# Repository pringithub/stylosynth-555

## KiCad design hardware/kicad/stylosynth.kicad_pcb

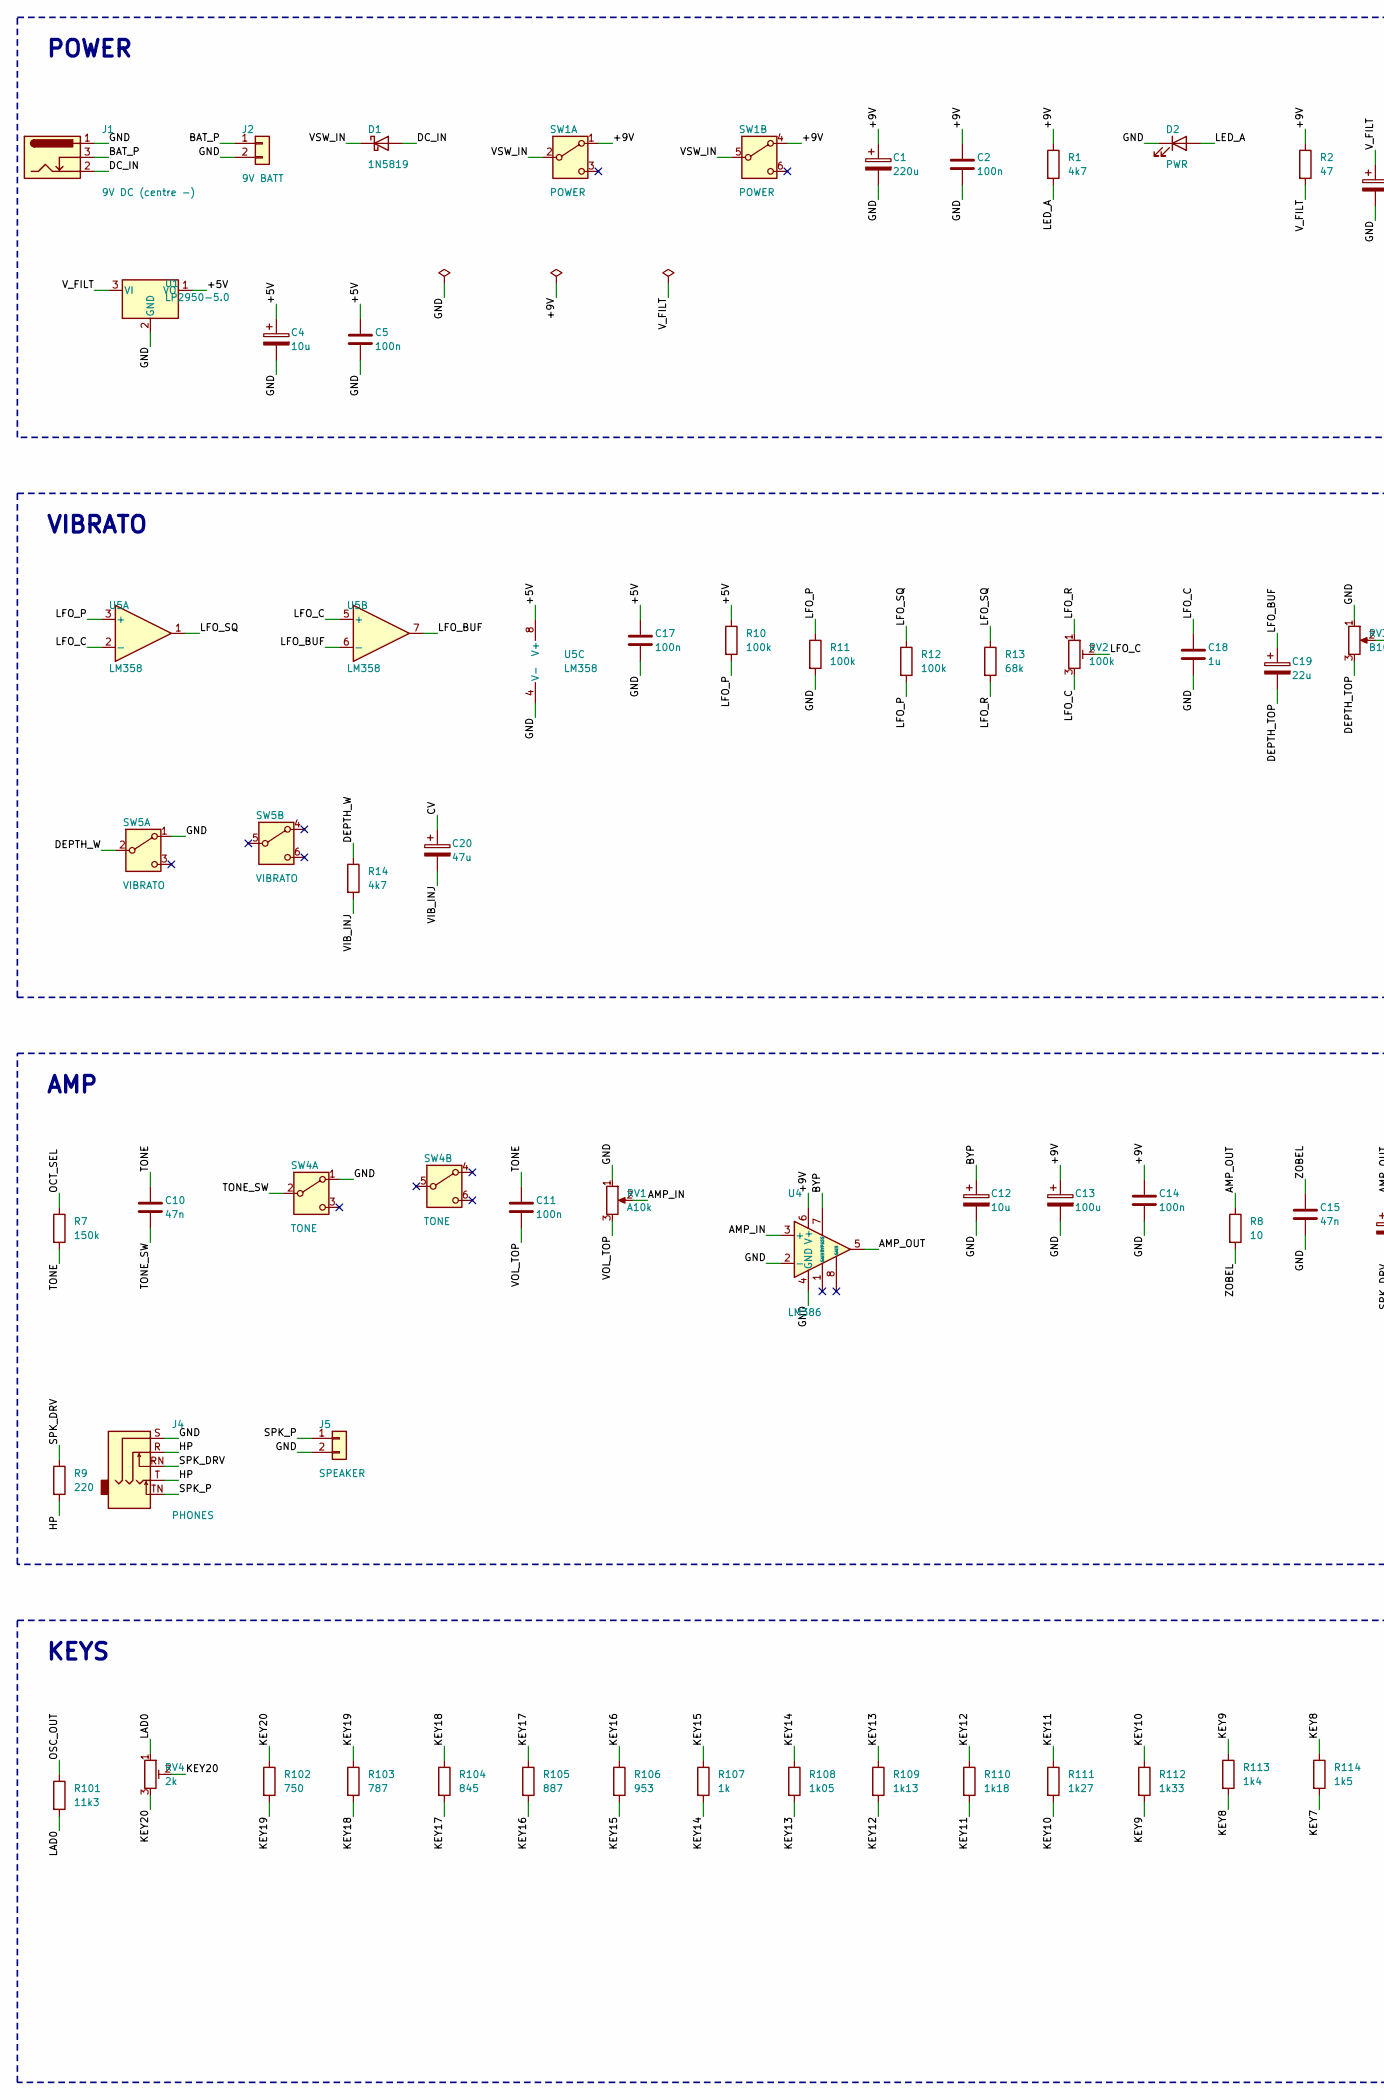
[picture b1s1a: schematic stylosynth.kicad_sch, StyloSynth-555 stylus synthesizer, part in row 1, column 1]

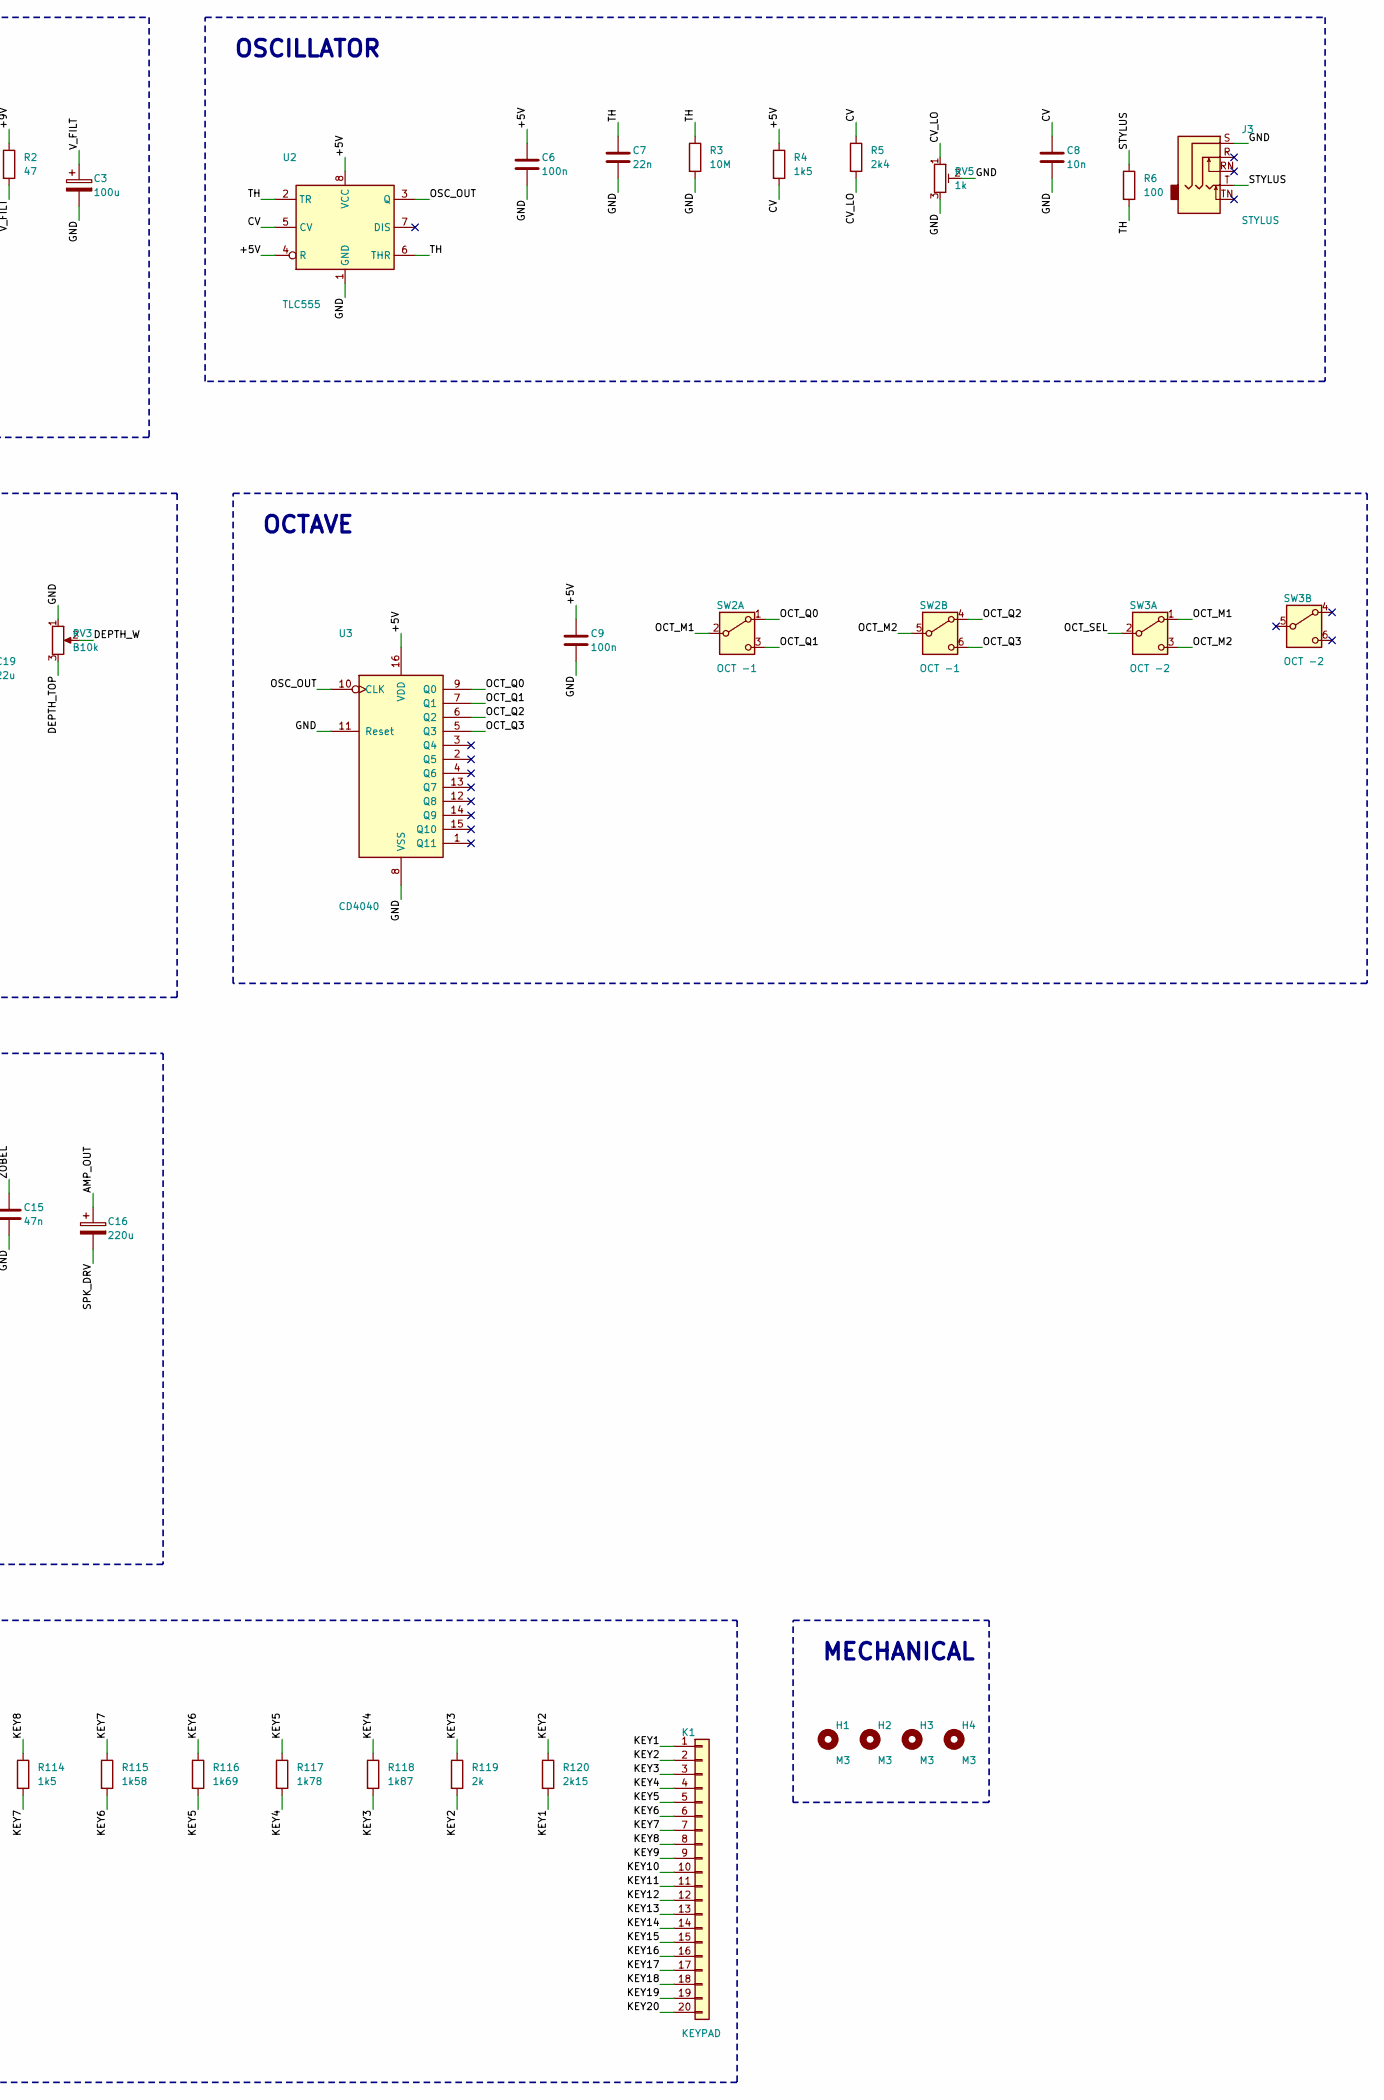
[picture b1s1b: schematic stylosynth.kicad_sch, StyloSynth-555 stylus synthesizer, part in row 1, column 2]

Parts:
C1, C16: 220u; CP_Radial_D8.0mm_P3.50mm
C2, C5, C6, C9, C14, C17: 100n; C_Disc_D5.0mm_W2.5mm_P5.00mm
C3, C13: 100u; CP_Radial_D6.3mm_P2.50mm
C4, C12: 10u; CP_Radial_D5.0mm_P2.00mm
C7: 22n; C_Rect_L7.2mm_W3.5mm_P5.00mm_FKS2_FKP2_MKS2_MKP2
C8: 10n; C_Disc_D5.0mm_W2.5mm_P5.00mm
C10: 47n; C_Rect_L7.2mm_W3.5mm_P5.00mm_FKS2_FKP2_MKS2_MKP2
C11: 100n; C_Rect_L7.2mm_W3.5mm_P5.00mm_FKS2_FKP2_MKS2_MKP2
C15: 47n; C_Disc_D5.0mm_W2.5mm_P5.00mm
C18: 1u; C_Rect_L7.2mm_W5.5mm_P5.00mm_FKS2_FKP2_MKS2_MKP2
C19: 22u; CP_Radial_D5.0mm_P2.00mm
C20: 47u; CP_Radial_D5.0mm_P2.00mm
D1: 1N5819; D_DO-41_SOD81_P5.08mm_Vertical_KathodeUp; MPN 1N5819
D2: PWR; LED_D3.0mm
H1, H2, H3, H4: M3; MountingHole_3.2mm_M3
J1: 9V DC (centre -); BarrelJack_CUI_PJ-102AH_Horizontal; MPN PJ-102AH
J2: 9V BATT; JST_XH_B2B-XH-A_1x02_P2.50mm_Vertical; MPN B2B-XH-A
J3: STYLUS; Jack_3.5mm_CUI_SJ1-3535NG_Horizontal; MPN SJ1-3535NG
J4: PHONES; Jack_3.5mm_CUI_SJ1-3535NG_Horizontal; MPN SJ1-3535NG
J5: SPEAKER; JST_XH_B2B-XH-A_1x02_P2.50mm_Vertical; MPN B2B-XH-A
K1: KEYPAD; KEYPAD_20
R1, R14: 4k7; R_Axial_DIN0207_L6.3mm_D2.5mm_P2.54mm_Vertical
R2: 47; R_Axial_DIN0207_L6.3mm_D2.5mm_P2.54mm_Vertical
R3: 10M; R_Axial_DIN0207_L6.3mm_D2.5mm_P2.54mm_Vertical
R4, R114: 1k5; R_Axial_DIN0207_L6.3mm_D2.5mm_P2.54mm_Vertical
R5: 2k4; R_Axial_DIN0207_L6.3mm_D2.5mm_P2.54mm_Vertical
R6: 100; R_Axial_DIN0207_L6.3mm_D2.5mm_P2.54mm_Vertical
R7: 150k; R_Axial_DIN0207_L6.3mm_D2.5mm_P2.54mm_Vertical
R8: 10; R_Axial_DIN0207_L6.3mm_D2.5mm_P2.54mm_Vertical
R9: 220; R_Axial_DIN0207_L6.3mm_D2.5mm_P2.54mm_Vertical
R10, R11, R12: 100k; R_Axial_DIN0207_L6.3mm_D2.5mm_P2.54mm_Vertical
R13: 68k; R_Axial_DIN0207_L6.3mm_D2.5mm_P2.54mm_Vertical
R101: 11k3; R_Axial_DIN0207_L6.3mm_D2.5mm_P2.54mm_Vertical
R102: 750; R_Axial_DIN0207_L6.3mm_D2.5mm_P2.54mm_Vertical
R103: 787; R_Axial_DIN0207_L6.3mm_D2.5mm_P2.54mm_Vertical
R104: 845; R_Axial_DIN0207_L6.3mm_D2.5mm_P2.54mm_Vertical
R105: 887; R_Axial_DIN0207_L6.3mm_D2.5mm_P2.54mm_Vertical
R106: 953; R_Axial_DIN0207_L6.3mm_D2.5mm_P2.54mm_Vertical
R107: 1k; R_Axial_DIN0207_L6.3mm_D2.5mm_P2.54mm_Vertical
R108: 1k05; R_Axial_DIN0207_L6.3mm_D2.5mm_P2.54mm_Vertical
R109: 1k13; R_Axial_DIN0207_L6.3mm_D2.5mm_P2.54mm_Vertical
R110: 1k18; R_Axial_DIN0207_L6.3mm_D2.5mm_P2.54mm_Vertical
R111: 1k27; R_Axial_DIN0207_L6.3mm_D2.5mm_P2.54mm_Vertical
R112: 1k33; R_Axial_DIN0207_L6.3mm_D2.5mm_P2.54mm_Vertical
R113: 1k4; R_Axial_DIN0207_L6.3mm_D2.5mm_P2.54mm_Vertical
R115: 1k58; R_Axial_DIN0207_L6.3mm_D2.5mm_P2.54mm_Vertical
R116: 1k69; R_Axial_DIN0207_L6.3mm_D2.5mm_P2.54mm_Vertical
R117: 1k78; R_Axial_DIN0207_L6.3mm_D2.5mm_P2.54mm_Vertical
R118: 1k87; R_Axial_DIN0207_L6.3mm_D2.5mm_P2.54mm_Vertical
R119: 2k; R_Axial_DIN0207_L6.3mm_D2.5mm_P2.54mm_Vertical
R120: 2k15; R_Axial_DIN0207_L6.3mm_D2.5mm_P2.54mm_Vertical
RV1: A10k; Potentiometer_Alps_RK09K_Single_Vertical; MPN RK09K1130A5R
RV2: 100k; Potentiometer_Bourns_3296W_Vertical; MPN 3296W-1-104
RV3: B10k; Potentiometer_Alps_RK09K_Single_Vertical; MPN RK09K1130A8G
RV4: 2k; Potentiometer_Bourns_3296W_Vertical; MPN 3296W-1-202LF
RV5: 1k; Potentiometer_Bourns_3296W_Vertical; MPN 3296W-1-102LF
SW1: POWER; SW_CK_JS202011CQN_DPDT_Straight; MPN JS202011CQN
SW2: OCT -1; SW_CK_JS202011CQN_DPDT_Straight; MPN JS202011CQN
SW3: OCT -2; SW_CK_JS202011CQN_DPDT_Straight; MPN JS202011CQN
SW4: TONE; SW_CK_JS202011CQN_DPDT_Straight; MPN JS202011CQN
SW5: VIBRATO; SW_CK_JS202011CQN_DPDT_Straight; MPN JS202011CQN
U1: LP2950-5.0; TO-92_Inline; MPN LP2950ACZ-5.0
U2: TLC555; DIP-8_W7.62mm_Socket; MPN TLC555CP
U3: CD4040; DIP-16_W7.62mm_Socket; MPN CD4040BE
U4: LM386; DIP-8_W7.62mm_Socket; MPN LM386N-1
U5: LM358; DIP-8_W7.62mm_Socket; MPN LM358P

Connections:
+5V: C4.1, C5.1, C6.1, C9.1, C17.1, R4.1, R10.1, U1.1 (VO), U2.4 (R), U2.8 (VCC), U3.16 (VDD), U5.8 (V+)
+9V: C1.1, C2.1, C13.1, C14.1, R1.1, R2.1, SW1.1 (A), SW1.4 (A), U4.6 (V+)
AMP_IN: RV1.2, U4.3 (+)
AMP_OUT: C16.1, R8.1, U4.5
BAT_P: J1.3, J2.1
BYP: C12.1, U4.7 (BYPASS)
CV: C8.1, C20.1, R4.2, R5.1, U2.5 (CV)
CV_LO: R5.2, RV5.1
DC_IN: D1.2 (A), J1.2
DEPTH_TOP: C19.2, RV3.3
DEPTH_W: R14.1, RV3.2, SW5.2 (B)
GND: C1.2, C2.2, C3.2, C4.2, C5.2, C6.2, C7.2, C8.2, C9.2, C12.2, C13.2, C14.2, C15.2, C17.2, C18.2, D2.1 (K), J1.1, J2.2, J3.S, J4.S, J5.2, R3.2, R11.2, RV1.1, RV3.1, RV5.2, RV5.3, SW4.1 (A), SW5.1 (A), U1.2 (GND), U2.1 (GND), U3.8 (VSS), U3.11 (Reset), U4.2 (-), U4.4 (GND), U5.4 (V-)
HP: J4.R, J4.T, R9.2
KEY1: K1.1, R120.2
KEY2: K1.2, R119.2, R120.1
KEY3: K1.3, R118.2, R119.1
KEY4: K1.4, R117.2, R118.1
KEY5: K1.5, R116.2, R117.1
KEY6: K1.6, R115.2, R116.1
KEY7: K1.7, R114.2, R115.1
KEY8: K1.8, R113.2, R114.1
KEY9: K1.9, R112.2, R113.1
KEY10: K1.10, R111.2, R112.1
KEY11: K1.11, R110.2, R111.1
KEY12: K1.12, R109.2, R110.1
KEY13: K1.13, R108.2, R109.1
KEY14: K1.14, R107.2, R108.1
KEY15: K1.15, R106.2, R107.1
KEY16: K1.16, R105.2, R106.1
KEY17: K1.17, R104.2, R105.1
KEY18: K1.18, R103.2, R104.1
KEY19: K1.19, R102.2, R103.1
KEY20: K1.20, R102.1, RV4.2, RV4.3
LAD0: R101.2, RV4.1
LED_A: D2.2 (A), R1.2
LFO_BUF: C19.1, U5.6 (-), U5.7
LFO_C: C18.1, RV2.2, RV2.3, U5.2 (-), U5.5 (+)
LFO_P: R10.2, R11.1, R12.2, U5.3 (+)
LFO_R: R13.2, RV2.1
LFO_SQ: R12.1, R13.1, U5.1
OCT_M1: SW2.2 (B), SW3.1 (A)
OCT_M2: SW2.5 (B), SW3.3 (C)
OCT_Q0: SW2.1 (A), U3.9 (Q0)
OCT_Q1: SW2.3 (C), U3.7 (Q1)
OCT_Q2: SW2.4 (A), U3.6 (Q2)
OCT_Q3: SW2.6 (C), U3.5 (Q3)
OCT_SEL: R7.1, SW3.2 (B)
OSC_OUT: R101.1, U2.3 (Q), U3.10 (CLK)
SPK_DRV: C16.2, J4.RN, R9.1
SPK_P: J4.TN, J5.1
STYLUS: J3.T, R6.1
TH: C7.1, R3.1, R6.2, U2.2 (TR), U2.6 (THR)
TONE: C10.1, C11.1, R7.2
TONE_SW: C10.2, SW4.2 (B)
VIB_INJ: C20.2, R14.2
VOL_TOP: C11.2, RV1.3
VSW_IN: D1.1 (K), SW1.2 (B), SW1.5 (B)
V_FILT: C3.1, R2.2, U1.3 (VI)
ZOBEL: C15.1, R8.2

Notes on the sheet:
POWER
OSCILLATOR
VIBRATO
OCTAVE
AMP
KEYS
MECHANICAL

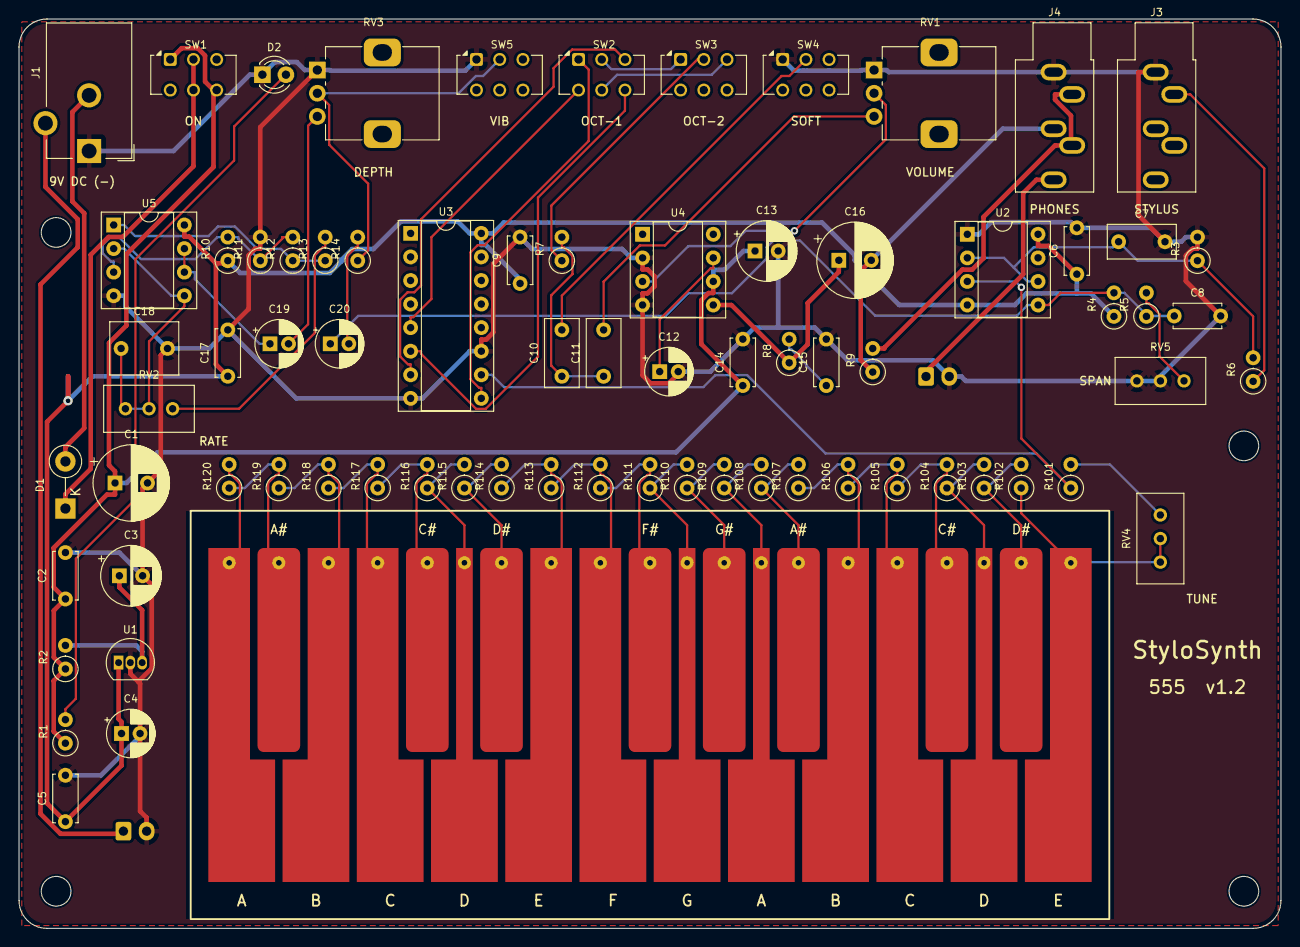
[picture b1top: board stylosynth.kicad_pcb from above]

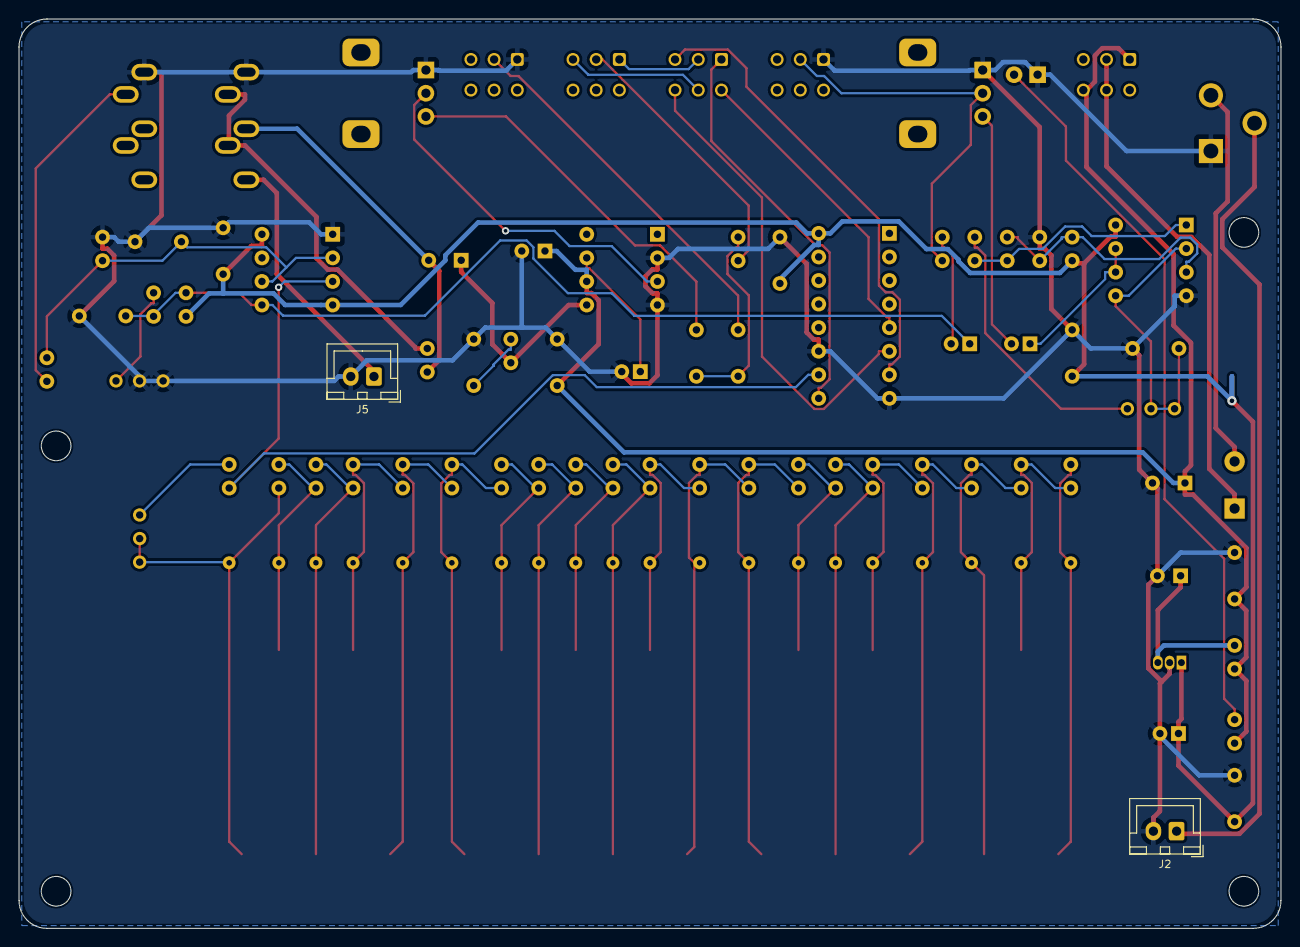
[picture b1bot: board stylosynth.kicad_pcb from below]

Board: 2 copper layers, 136.0 x 98.0 mm, 81 parts (2 on the bottom side), 59 nets.

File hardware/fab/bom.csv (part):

Qty,References,Value,Description,Footprint,Manufacturer,MPN,Verify,Est. unit USD,Est. line USD
2,"C1, C16",220u,"Capacitor, electrolytic 220uF 16V",CP_Radial_D8.0mm_P3.50mm,Panasonic,"EEU-FC1C221 (220uF 16V, 8 mm, 3.5 mm pitch)",yes,0.45,0.90
6,"C2, C5, C6, C9, C14, C17",100n,"Capacitor, ceramic X7R 50V",C_Disc_D5.0mm_W2.5mm_P5.00mm,KEMET,C322C104K5R5TA,yes,0.25,1.50
2,"C3, C13",100u,"Capacitor, electrolytic 100uF 16V",CP_Radial_D6.3mm_P2.50mm,Panasonic,"EEU-FC1C101 (100uF 16V, 6.3 mm, 2.5 mm pitch)",yes,0.35,0.70
2,"C4, C12",10u,"Capacitor, electrolytic 10uF 25V",CP_Radial_D5.0mm_P2.00mm,Panasonic,"EEU-FC1E100 (10uF 25V, 5 mm, 2 mm pitch)",yes,0.25,0.50
1,C7,22n,"Capacitor, polypropylene film 22nF 2.5% 100V (timing)",C_Rect_L7.2mm_W3.5mm_P5.00mm_FKS2_FKP2_MKS2_MKP2,WIMA,MKP2 22nF 100V 2.5% 5 mm (polypropylene),yes,0.60,0.60
1,C8,10n,"Capacitor, ceramic X7R 50V",C_Disc_D5.0mm_W2.5mm_P5.00mm,KEMET,C322C103K5R5TA,yes,0.25,0.25
1,C10,47n,"Capacitor, polyester film 47nF 63V",C_Rect_L7.2mm_W3.5mm_P5.00mm_FKS2_FKP2_MKS2_MKP2,WIMA,MKS2 47nF 63V 5 mm,yes,0.35,0.35
1,C11,100n,"Capacitor, polyester film 100nF 63V",C_Rect_L7.2mm_W3.5mm_P5.00mm_FKS2_FKP2_MKS2_MKP2,WIMA,MKS2 100nF 63V 5 mm,yes,0.35,0.35
1,C15,47n,"Capacitor, ceramic X7R 50V",C_Disc_D5.0mm_W2.5mm_P5.00mm,KEMET,C322C473K5R5TA,yes,0.25,0.25
1,C18,1u,"Capacitor, polyester film 1uF 63V",C_Rect_L7.2mm_W5.5mm_P5.00mm_FKS2_FKP2_MKS2_MKP2,WIMA,MKS2 1uF 63V 5 mm,yes,0.60,0.60
1,C19,22u,"Capacitor, aluminium electrolytic 25V",CP_Radial_D5.0mm_P2.00mm,Panasonic,"EEU-FC1E220 (22uF 25V, 5 mm, 2 mm pitch)",yes,0.30,0.30
1,C20,47u,"Capacitor, aluminium electrolytic 25V",CP_Radial_D5.0mm_P2.00mm,Panasonic,"47uF 16V, 5 mm dia, 2 mm pitch (FC/FR series)",yes,0.30,0.30
1,D1,1N5819,Schottky diode 40V 1A (reverse-polarity protection),D_DO-41_SOD81_P5.08mm_Vertical_KathodeUp,onsemi / Vishay,1N5819,no,0.20,0.20
1,D2,PWR,"LED 3mm red, diffused",LED_D3.0mm,Kingbright,WP710A10ID (3 mm red diffused),yes,0.25,0.25
1,J1,9V DC (centre -),"DC barrel jack 2.1mm with switch, CUI PJ-102AH",BarrelJack_CUI_PJ-102AH_Horizontal,Same Sky (CUI),PJ-102AH (5.5x2.1 mm),yes,0.90,0.90
1,J2,9V BATT,JST XH 2-pin header (9V battery snap),JST_XH_B2B-XH-A_1x02_P2.50mm_Vertical,JST,B2B-XH-A(LF)(SN),no,0.15,0.15
1,J3,STYLUS,"3.5mm TRS jack horizontal, switched, CUI SJ1-3535NG",Jack_3.5mm_CUI_SJ1-3535NG_Horizontal,Same Sky (CUI),SJ1-3535NG,no,1.30,1.30
1,J4,PHONES,"3.5mm TRS jack horizontal, switched, CUI SJ1-3535NG",Jack_3.5mm_CUI_SJ1-3535NG_Horizontal,Same Sky (CUI),SJ1-3535NG,no,1.30,1.30
1,J5,SPEAKER,JST XH 2-pin header (speaker),JST_XH_B2B-XH-A_1x02_P2.50mm_Vertical,JST,B2B-XH-A(LF)(SN),no,0.15,0.15
2,"R1, R14",4k7,"Resistor, metal film 1% 0.25W",R_Axial_DIN0207_L6.3mm_D2.5mm_P2.54mm_Vertical,Yageo / generic,4k7 metal film 1% 0.25 W (e.g. Yageo MFR-25 series),no,0.03,0.06
1,R2,47,"Resistor, metal film 1% 0.25W",R_Axial_DIN0207_L6.3mm_D2.5mm_P2.54mm_Vertical,Yageo / generic,47 metal film 1% 0.25 W (e.g. Yageo MFR-25 series),no,0.03,0.03
1,R3,10M,"Resistor, metal film 1% 0.25W",R_Axial_DIN0207_L6.3mm_D2.5mm_P2.54mm_Vertical,Yageo / generic,10M metal film 1% 0.25 W (e.g. Yageo MFR-25 series),no,0.03,0.03
2,"R4, R114",1k5,"Resistor, metal film 1% 0.25W",R_Axial_DIN0207_L6.3mm_D2.5mm_P2.54mm_Vertical,Yageo / generic,1k5 metal film 1% 0.25 W (e.g. Yageo MFR-25 series),no,0.03,0.06
1,R5,2k4,"Resistor, metal film 1% 0.25W",R_Axial_DIN0207_L6.3mm_D2.5mm_P2.54mm_Vertical,Yageo / generic,2k4 metal film 1% 0.25 W (e.g. Yageo MFR-25 series),no,0.03,0.03
1,R6,100,"Resistor, metal film 1% 0.25W",R_Axial_DIN0207_L6.3mm_D2.5mm_P2.54mm_Vertical,Yageo / generic,100 metal film 1% 0.25 W (e.g. Yageo MFR-25 series),no,0.03,0.03
1,R7,150k,"Resistor, metal film 1% 0.25W",R_Axial_DIN0207_L6.3mm_D2.5mm_P2.54mm_Vertical,Yageo / generic,150k metal film 1% 0.25 W (e.g. Yageo MFR-25 series),no,0.03,0.03
1,R8,10,"Resistor, metal film 1% 0.25W",R_Axial_DIN0207_L6.3mm_D2.5mm_P2.54mm_Vertical,Yageo / generic,10 metal film 1% 0.25 W (e.g. Yageo MFR-25 series),no,0.03,0.03
1,R9,220,"Resistor, metal film 1% 0.25W",R_Axial_DIN0207_L6.3mm_D2.5mm_P2.54mm_Vertical,Yageo / generic,220 metal film 1% 0.25 W (e.g. Yageo MFR-25 series),no,0.03,0.03
3,"R10, R11, R12",100k,"Resistor, metal film 1% 0.25W",R_Axial_DIN0207_L6.3mm_D2.5mm_P2.54mm_Vertical,Yageo / generic,100k metal film 1% 0.25 W (e.g. Yageo MFR-25 series),no,0.03,0.09
1,R13,68k,"Resistor, metal film 1% 0.25W",R_Axial_DIN0207_L6.3mm_D2.5mm_P2.54mm_Vertical,Yageo / generic,68k metal film 1% 0.25 W (e.g. Yageo MFR-25 series),no,0.03,0.03
1,R101,11k3,"Resistor, metal film 1% 0.25W",R_Axial_DIN0207_L6.3mm_D2.5mm_P2.54mm_Vertical,Yageo / generic,11k3 metal film 1% 0.25 W (e.g. Yageo MFR-25 series),no,0.03,0.03
1,R102,750,"Resistor, metal film 1% 0.25W",R_Axial_DIN0207_L6.3mm_D2.5mm_P2.54mm_Vertical,Yageo / generic,750 metal film 1% 0.25 W (e.g. Yageo MFR-25 series),no,0.03,0.03
1,R103,787,"Resistor, metal film 1% 0.25W",R_Axial_DIN0207_L6.3mm_D2.5mm_P2.54mm_Vertical,Yageo / generic,787 metal film 1% 0.25 W (e.g. Yageo MFR-25 series),no,0.03,0.03
1,R104,845,"Resistor, metal film 1% 0.25W",R_Axial_DIN0207_L6.3mm_D2.5mm_P2.54mm_Vertical,Yageo / generic,845 metal film 1% 0.25 W (e.g. Yageo MFR-25 series),no,0.03,0.03
1,R105,887,"Resistor, metal film 1% 0.25W",R_Axial_DIN0207_L6.3mm_D2.5mm_P2.54mm_Vertical,Yageo / generic,887 metal film 1% 0.25 W (e.g. Yageo MFR-25 series),no,0.03,0.03
1,R106,953,"Resistor, metal film 1% 0.25W",R_Axial_DIN0207_L6.3mm_D2.5mm_P2.54mm_Vertical,Yageo / generic,953 metal film 1% 0.25 W (e.g. Yageo MFR-25 series),no,0.03,0.03
1,R107,1k,"Resistor, metal film 1% 0.25W",R_Axial_DIN0207_L6.3mm_D2.5mm_P2.54mm_Vertical,Yageo / generic,1k metal film 1% 0.25 W (e.g. Yageo MFR-25 series),no,0.03,0.03
1,R108,1k05,"Resistor, metal film 1% 0.25W",R_Axial_DIN0207_L6.3mm_D2.5mm_P2.54mm_Vertical,Yageo / generic,1k05 metal film 1% 0.25 W (e.g. Yageo MFR-25 series),no,0.03,0.03
1,R109,1k13,"Resistor, metal film 1% 0.25W",R_Axial_DIN0207_L6.3mm_D2.5mm_P2.54mm_Vertical,Yageo / generic,1k13 metal film 1% 0.25 W (e.g. Yageo MFR-25 series),no,0.03,0.03
1,R110,1k18,"Resistor, metal film 1% 0.25W",R_Axial_DIN0207_L6.3mm_D2.5mm_P2.54mm_Vertical,Yageo / generic,1k18 metal film 1% 0.25 W (e.g. Yageo MFR-25 series),no,0.03,0.03
1,R111,1k27,"Resistor, metal film 1% 0.25W",R_Axial_DIN0207_L6.3mm_D2.5mm_P2.54mm_Vertical,Yageo / generic,1k27 metal film 1% 0.25 W (e.g. Yageo MFR-25 series),no,0.03,0.03
1,R112,1k33,"Resistor, metal film 1% 0.25W",R_Axial_DIN0207_L6.3mm_D2.5mm_P2.54mm_Vertical,Yageo / generic,1k33 metal film 1% 0.25 W (e.g. Yageo MFR-25 series),no,0.03,0.03
1,R113,1k4,"Resistor, metal film 1% 0.25W",R_Axial_DIN0207_L6.3mm_D2.5mm_P2.54mm_Vertical,Yageo / generic,1k4 metal film 1% 0.25 W (e.g. Yageo MFR-25 series),no,0.03,0.03
1,R115,1k58,"Resistor, metal film 1% 0.25W",R_Axial_DIN0207_L6.3mm_D2.5mm_P2.54mm_Vertical,Yageo / generic,1k58 metal film 1% 0.25 W (e.g. Yageo MFR-25 series),no,0.03,0.03
1,R116,1k69,"Resistor, metal film 1% 0.25W",R_Axial_DIN0207_L6.3mm_D2.5mm_P2.54mm_Vertical,Yageo / generic,1k69 metal film 1% 0.25 W (e.g. Yageo MFR-25 series),no,0.03,0.03
1,R117,1k78,"Resistor, metal film 1% 0.25W",R_Axial_DIN0207_L6.3mm_D2.5mm_P2.54mm_Vertical,Yageo / generic,1k78 metal film 1% 0.25 W (e.g. Yageo MFR-25 series),no,0.03,0.03
1,R118,1k87,"Resistor, metal film 1% 0.25W",R_Axial_DIN0207_L6.3mm_D2.5mm_P2.54mm_Vertical,Yageo / generic,1k87 metal film 1% 0.25 W (e.g. Yageo MFR-25 series),no,0.03,0.03
1,R119,2k,"Resistor, metal film 1% 0.25W",R_Axial_DIN0207_L6.3mm_D2.5mm_P2.54mm_Vertical,Yageo / generic,2k metal film 1% 0.25 W (e.g. Yageo MFR-25 series),no,0.03,0.03
1,R120,2k15,"Resistor, metal film 1% 0.25W",R_Axial_DIN0207_L6.3mm_D2.5mm_P2.54mm_Vertical,Yageo / generic,2k15 metal film 1% 0.25 W (e.g. Yageo MFR-25 series),no,0.03,0.03
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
